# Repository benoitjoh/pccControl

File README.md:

# PhaseCutControl #

Library to make usage of a phase cut controller with a ATMEGA easier.
attached you find a circuit with a layout example for a small board for the unit.

The modules uses
* timer1 with prescaler 8 and needs the OCR1A interrupt.
* pin 2 or pin 3 as external interrupt input source
* one digital out to fire the triac

## /!\ WARNING

```
/!\ Dealing with high voltage is dangerous. Be careful and know what you can do and what you better leave. /!\
```

## Installation ##

Just copy the folder PhaseCutCtrl with c++ sources in library folder from ArduinoIDE

## Principle ##

For basic overview see: [>> phase cut control on wikipedia](https://en.wikipedia.org/wiki/Phase-fired_controllers)

In the picture the idea is shown. The trick is to detect the start point of the curve. therefor the zerodetection unit in the circuit works out a clean enough signal with the opcocoupler 4N35 and a PNP transistor.
The signal triggers an external interrupt which sets the timer1 to zero.
Now, depending from the power value, a delay is calculated and set to outputCompareRegister1a (OCR1A). The interrupt triggers a short pulse on the output pin (blue spice in the picture) and fires the triac (red curve) via the MOC3022 optocoupler. The triac is on until the AC voltage returns to zero point, and shuts of in that moment. So the load gets only the energy of grey part under the graph.
(one mistake in the picture is, that the second wave should be negative, because its alternating current of course..)

## Usage ##

### Initialization
The class is per initialized in the cpp file during compilation. This is neccessary because the interrupt method needs to know which method of the class it must call.
So the initializt() method has to be called in setup() to pass parameters.

```c++
#include <PhaseCutCtrl.h>
#define PIN_IN_ACZERO_SIGNAL   3  // pin for AC zeropoint detection (Interrupt source, so can only be 2 or 3)
#define PIN_PCC_OUT_A          4  // pin for pulse cut modulation output

// NOTE: the class is preinstanciated as PCCtrl.

void setup()
{
    // Phase cut Ctrl module
    PCCtrl.initialize(PIN_IN_ACZERO_SIGNAL, PIN_PCC_OUT_A);
}

```

### set the power ###

To set the power value, call set_pcc(power). run it as seldom as possible to reduce timeconsumption for the float calculations.
In the example, a function returns true, when it changed the targetpower:

The value of power is between 0 (off) and 2048 (max).

```c++
//  use something like

if (someFunctionThatDefinespower())
{
    PCCtrl.set_pcc(power);
}

```
## Use the waitUntilAcZero() method for relais

This Method waits in a loop until the AC curve hits the x axis at zero Volt.

In exactly that moment you can switch a triac and you have a solid state relais :-)

If you use a mechanical relais, you have to consider the delay of the switch. 

```c++
//  use a wrapper like this to swap the pin that conects to the relais

void digitalWriteAtSolidState(byte mypin, byte myvalue)
{
    PCCtrl.waitUntilAcZero(TIME_DELAY_RELAIS_MICROS);
    digitalWrite(mypin, myvalue);
}

```
the value of myDelay depends of lazyness of the mechanical component. the function waits a bit, then fires and the switch will open/close in the next zero Volt phase. (for a triac it is 0, my small standard 12V relais has 11000 mySecs)

## Net Frequency Measurement
(It needs about 1k program memory extra.)

calling
```c++
float PCCtlr.getNetFreq()
```
calculates the time for one event and returns transfored to Hertz.

With 
```c++
float PCCtlr.acNetIsAlive()
```
You can detect if the system is seperated from AC supply. If no alternating current is on for 300ms the function returns false.
A good moment to quickly store some data in eeprom before the controller stops working... 

(c) [Johannes Benoit 2018](mailto:jbenoit@t-online.de)

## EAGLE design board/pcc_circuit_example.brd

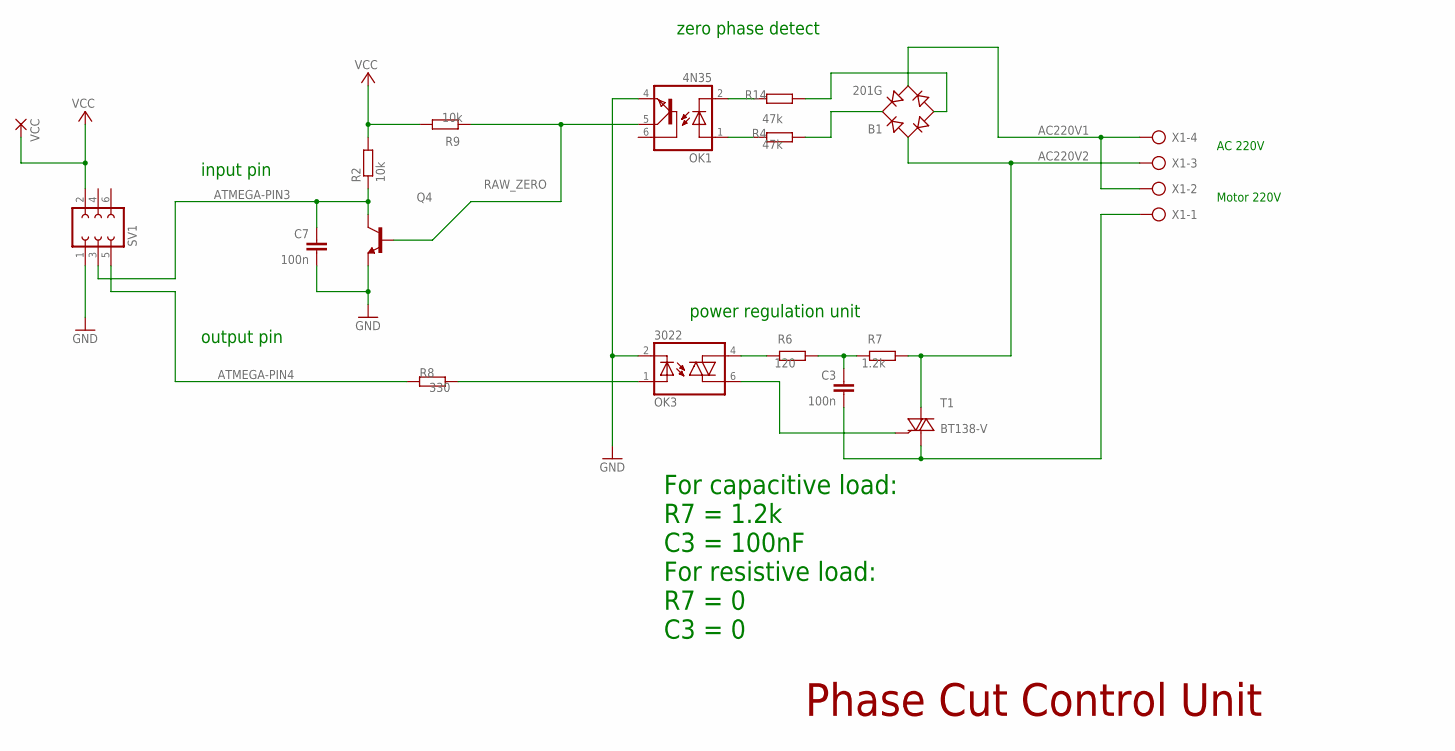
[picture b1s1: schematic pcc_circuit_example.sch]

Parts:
B1: 201G; RB1A
C3: 100n; C15B5
C7: 100n; C050-024X044
OK1: 4N35; DIL06
OK3: 3022; DIL06
Q4: BC548; TO92-EBC
R2, R9: 10k; R_0207/2V
R4, R14: 47k; R_0207/2V
R6: 120; R_0207/2V
R7: 1.2k; R_0207/2V
R8: 330; R_0207/2V
SV1: FE03-2
T1: BT138-V; TO220V
VCC: PAD1,6/0,8
X1: AK300/4

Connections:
220V_LOAD: C3.2, T1.1 (A1), X1.1
AC220V1: B1.AC2, X1.2, X1.4
AC220V2: B1.AC1, R7.2, T1.2 (A2), X1.3
ATMEGA-PIN3: C7.1, Q4.C, R2.1, SV1.3
ATMEGA-PIN4: R8.2, SV1.5
GND: C7.2, OK1.4 (EMI), OK3.2 (C), Q4.E, SV1.1
unnamed: B1.+, R4.2
unnamed: B1.-, R14.2
unnamed: OK3.6 (A2), T1.3 (G)
unnamed: OK1.2 (C), R14.1
unnamed: OK1.1 (A), R4.1
unnamed: OK3.1 (A), R8.1
unnamed: C3.1, R6.2, R7.1
unnamed: OK3.4 (A1), R6.1
RAW_ZERO: OK1.5 (COL), Q4.B, R9.1
VCC: R2.2, R9.2, SV1.2, VCC.1

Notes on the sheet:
Motor 220V
AC 220V
input pin
output pin
Phase Cut Control Unit
zero phase detect
power regulation unit
For capacitive load: R7 = 1.2k C3 = 100nF For resistive load: R7 = 0 C3 = 0

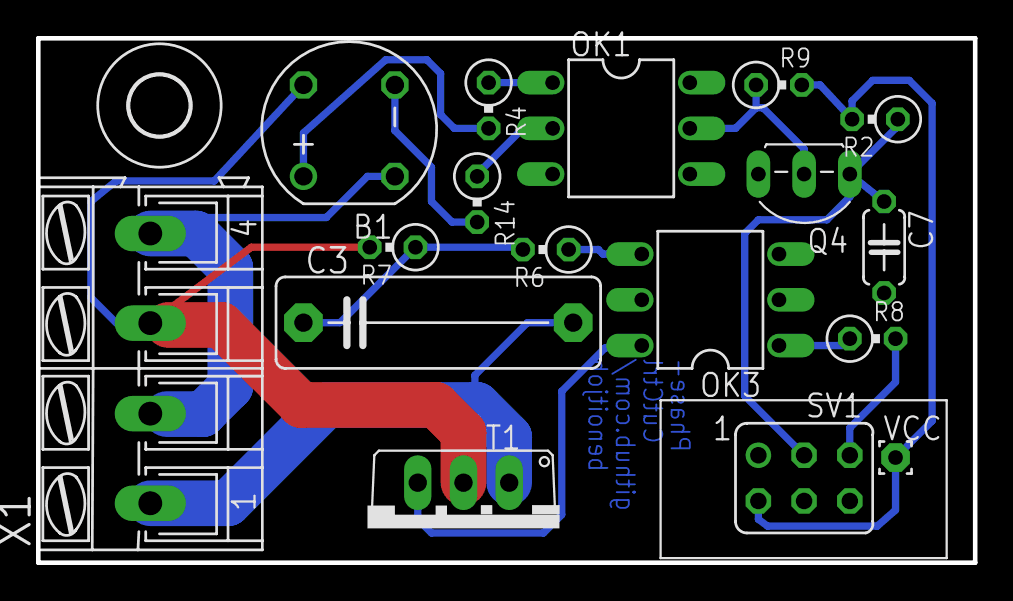
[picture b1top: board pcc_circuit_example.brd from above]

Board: 2 copper layers, 52.0 x 29.1 mm, 18 parts (0 on the bottom side), 16 nets.

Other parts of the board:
U$3: 3,3

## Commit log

2018-10-13 initial version
2018-10-14 installation note, move code in subfolder for easier installation
2018-10-15 printable version of boardlayout
2018-10-17 correct paths, reduce width of board, to get two in one euro format with 5mm spacer
2018-10-21 a bit more space..
2018-11-06 docu, finetuning
2018-11-26 little improvements
2018-11-26 save variables
2018-11-26 add generated pdf files for layouts
2019-01-06 generator for precalculated maping table
2019-01-06 adjust to new system and gerbmerge
2019-01-07 reduce number of drilltools
2019-01-16 new technique of mapping the power with a precalculated set of sinus values
2019-01-17 unset debug
2019-01-17 simplify structure
2019-01-21 perform regulation only if pcc_power has changed and neither 0 nor max power
2019-10-23 small changes
2019-10-23 new function waitUntilAzZero() as service to allow relais to be switched on solid state of alternating current
2019-10-23 documentation
2019-10-23 update eps print files automaticly
2019-10-26 refactor netFrequency measurement to use the counter directly; use TCNT1 as condition for solid state
2019-10-27 pass parameter offsetMy to get out earlyier
2019-11-04 reduce noise on aclow wire by defining a minimum counter to fire the event
